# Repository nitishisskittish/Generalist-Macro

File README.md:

## **Astrapad**
---
A 7 key macropad with a rotary encoder, OLED screen, and 16 WS2812B LED’s. Currently runs on KMK firmware

### **Features**
---
- Two Piece 3D Printable Case
- 128x32 OLED Display
- EC11 Rotary encoder
- 16 WS2812B RGB LEDs, probably waaayyy too much, but the more the merrier I guess
- 7 Keys

### **CAD Model**
---
The case is held together by 4 M3 Bolts and heatset inserts, 1 in each corner. The bottom half of the case has a built in tilt. Originally I designed this with see-through plastic “windows” in mind, but as of now those windows have been replaced with direct holes looking into the PCB. Maybe I’ll add them later.

### **PCB**
---
I made my PCB in KiCad. I got the bangboo silkscreen arts from the [Zenless Zone Zero Fandom Sticker Page](https://zenless-zone-zero.fandom.com/wiki/Stickers), and the pikachu art from [pixlecheese](https://www.pixilart.com/art/pikachu-thunderbolt-1a236168d6612c3)

- Schematic:

- PCB:

- My favorite part of the whole project tbh, made me feel very smart. Also if you're interested the numbers at the very bottom are binary, although it doesn’t spell out anything that interesting

### **Firmware**
---
Currently Astrapad runs on KMK, but I plan on switching to QMK later because I want to add [VIA](https://caniusevia.com/) support
- The rotary encoder changes the volume, and you can tap it to toggle mute
- The top left and top right keys skips forward or backward respectively in the playback queue
- The top middle button and bottom 3 buttons act as WASD keys, with the top middle button being the W Key
- The bottom right button is currently mapped to a custom shortcut I have on my computer that opens Spotify
- The OLED Screen displays the current volume level of whatever device the macropad is currently connected to
- I have a list of features I want to add commented in the KMK main.py file if you're interested in that
### **BOM**
---
- 1x Seeed XIAO RP2040
- 1x 0.91 inch OLED displays 
- 1x EC11 rotary encoders
- 1x Case (2 3D printed parts)
- 1x 3D printed EC11 (Rotary Encoder) Knob
- 4x M3x5x4 Heatset inserts
- 4x M3x16mm screws
- 7x Cherry MX Switches
- 7x DSA keycaps
- 8x Through-hole 1N4148 Diodes
- 16x SK6812 MINI-E LEDs

### **Extra Stuff**
---
The example I’m basing this README off of had this section, so I’m adding it too. 
Thanks a lot to the Blueprint Hackclub slack, I probably wouldn’t have finished this project without their help.
Ummm yeah, that’s it I guess.

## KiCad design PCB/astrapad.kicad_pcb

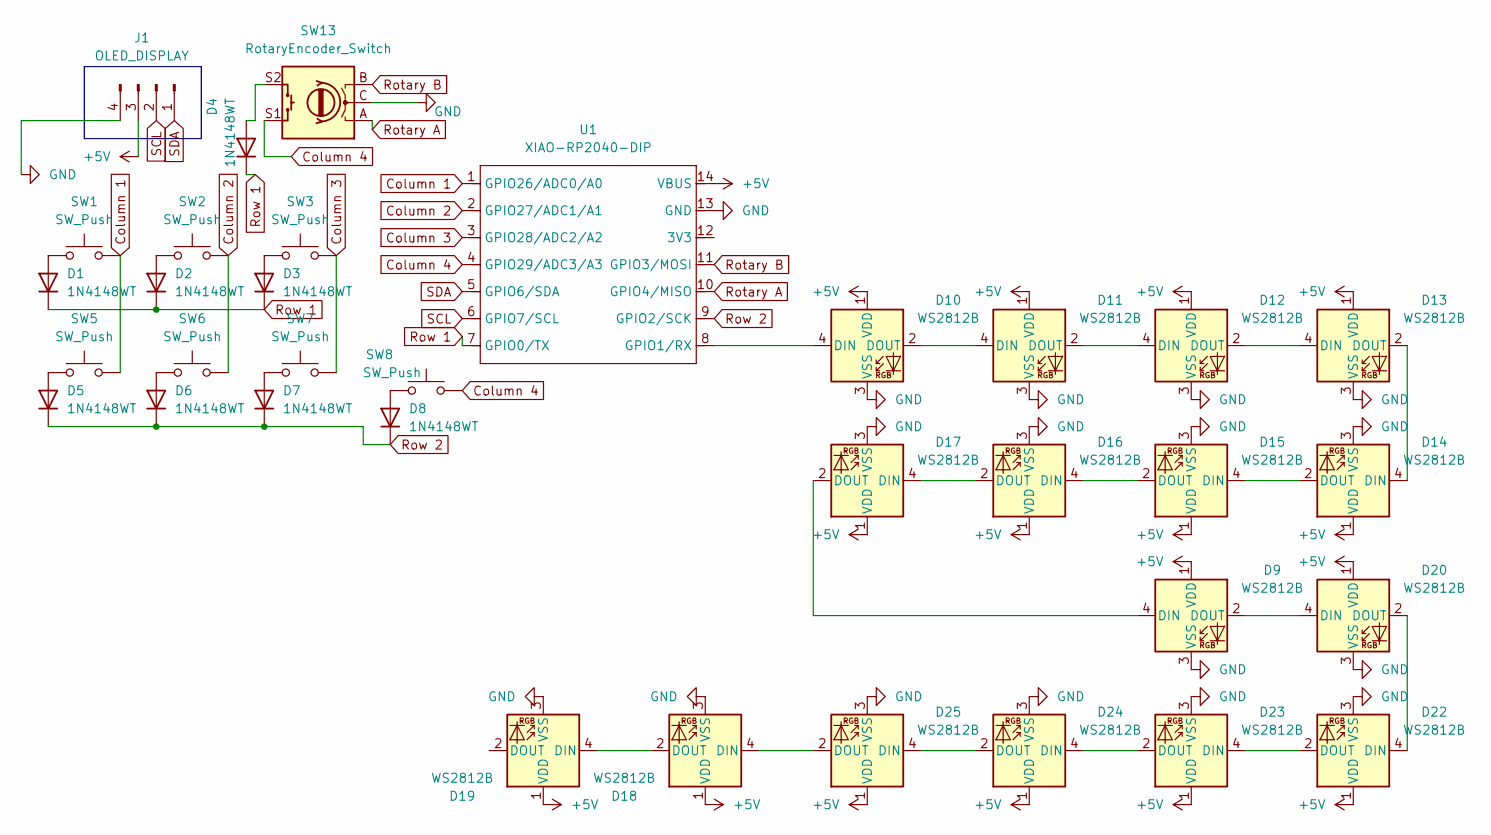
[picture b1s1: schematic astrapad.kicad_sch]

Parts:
D1, D2, D3, D4, D5, D6, D7, D8: 1N4148WT; D_SOD-523
D9, D17, D18, D19, D20, D22, D23, D24, D25: WS2812B; LED_SK6812MINI_PLCC4_3.5x3.5mm_P1.75mm
D10, D11, D12, D13, D14, D15, D16: WS2812B; MX_SK6812MINI-E_REV
J1: OLED_DISPLAY; PinHeader_1x04_P2.54mm_Vertical
SW1, SW2, SW3, SW5, SW6, SW7, SW8: SW_Push; SW_Cherry_MX_1.00u_PCB
SW13: RotaryEncoder_Switch; RotaryEncoder_Alps_EC11E-Switch_Vertical_H20mm
U1: XIAO-RP2040-DIP

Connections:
+5V: D9.1 (VDD), D10.1 (VDD), D11.1 (VDD), D12.1 (VDD), D13.1 (VDD), D14.1 (VDD), D15.1 (VDD), D16.1 (VDD), D17.1 (VDD), D18.1 (VDD), D19.1 (VDD), D20.1 (VDD), D22.1 (VDD), D23.1 (VDD), D24.1 (VDD), D25.1 (VDD), J1.3, U1.14 (VBUS)
Column 1: SW1.2, SW5.2, U1.1 (GPIO26/ADC0/A0)
Column 2: SW2.2, SW6.2, U1.2 (GPIO27/ADC1/A1)
Column 3: SW3.2, SW7.2, U1.3 (GPIO28/ADC2/A2)
Column 4: SW8.2, SW13.S1, U1.4 (GPIO29/ADC3/A3)
GND: D9.3 (VSS), D10.3 (VSS), D11.3 (VSS), D12.3 (VSS), D13.3 (VSS), D14.3 (VSS), D15.3 (VSS), D16.3 (VSS), D17.3 (VSS), D18.3 (VSS), D19.3 (VSS), D20.3 (VSS), D22.3 (VSS), D23.3 (VSS), D24.3 (VSS), D25.3 (VSS), J1.4, SW13.C, U1.13 (GND)
unnamed: D1.2 (A), SW1.1
unnamed: D2.2 (A), SW2.1
unnamed: D3.2 (A), SW3.1
unnamed: D4.2 (A), SW13.S2
unnamed: D5.2 (A), SW5.1
unnamed: D6.2 (A), SW6.1
unnamed: D7.2 (A), SW7.1
unnamed: D8.2 (A), SW8.1
unnamed: D10.4 (DIN), U1.8 (GPIO1/RX)
unnamed: D10.2 (DOUT), D11.4 (DIN)
unnamed: D11.2 (DOUT), D12.4 (DIN)
unnamed: D12.2 (DOUT), D13.4 (DIN)
unnamed: D13.2 (DOUT), D14.4 (DIN)
unnamed: D14.2 (DOUT), D15.4 (DIN)
unnamed: D15.2 (DOUT), D16.4 (DIN)
unnamed: D16.2 (DOUT), D17.4 (DIN)
unnamed: D9.4 (DIN), D17.2 (DOUT)
unnamed: D18.4 (DIN), D25.2 (DOUT)
unnamed: D18.2 (DOUT), D19.4 (DIN)
unnamed: D9.2 (DOUT), D20.4 (DIN)
unnamed: D20.2 (DOUT), D22.4 (DIN)
unnamed: D22.2 (DOUT), D23.4 (DIN)
unnamed: D23.2 (DOUT), D24.4 (DIN)
unnamed: D24.2 (DOUT), D25.4 (DIN)
Rotary A: SW13.A, U1.10 (GPIO4/MISO)
Rotary B: SW13.B, U1.11 (GPIO3/MOSI)
Row 1: D1.1 (K), D2.1 (K), D3.1 (K), D4.1 (K), U1.7 (GPIO0/TX)
Row 2: D5.1 (K), D6.1 (K), D7.1 (K), D8.1 (K), U1.9 (GPIO2/SCK)
SCL: J1.2, U1.6 (GPIO7/SCL)
SDA: J1.1, U1.5 (GPIO6/SDA)

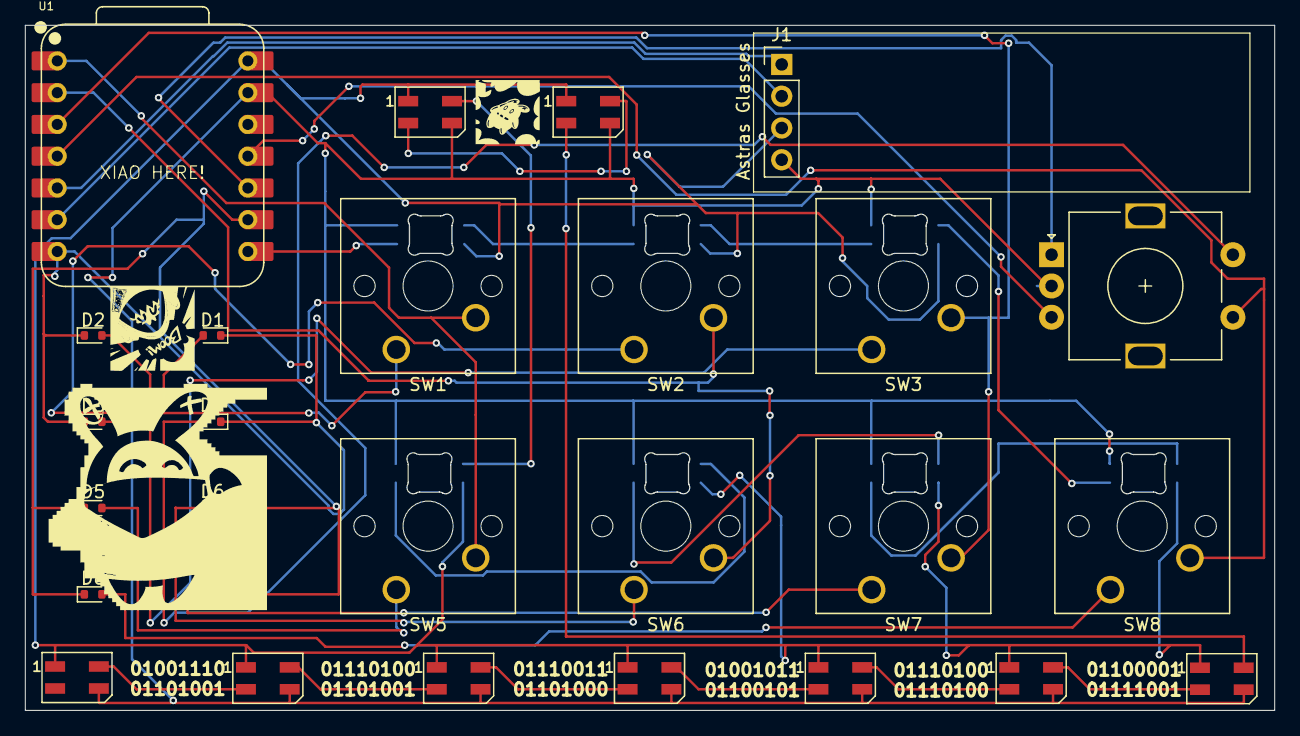
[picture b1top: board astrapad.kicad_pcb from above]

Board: 2 copper layers, 99.8 x 54.7 mm, 34 parts (0 on the bottom side), 36 nets.

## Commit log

2025-11-29 Finished Schematic, Started PCB
2025-11-30 PCB laid out and wired. I just have to add the **Aesthetic** silkscreens now
2025-12-06 Fixed 3D Model of PCB in FreeCAD Turns out the knob isn't centered properly, so I'll have to fix that later. In other news, I really shouldn't be awake this late...
2025-12-07 Switching from FreeCAD to Fusion360 Due to the several and constant issues I'm having with FreeCAD, I will be switching to Fusion360 If you wish to know why I was using FreeCAD in the first place, it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
2025-12-11 Repositioned Key Backlight LEDS
2025-12-12 Some PCB Rerouting And by "some", I mean all of it. I didn't account for the size of the actual OLED screen (just had the pins before), so I had to reroute basically everything once I did.
2025-12-20 Forgot to export with tracks
2025-12-22 Case finished, going to start working on readme, syncing to desktop
2025-12-22 A merge tragedy occurred...
2025-12-22 Yeah....I forgot to update the footprints after updating the paths. Also all these commits are happening because I'm syncing files between my laptop and desktop through git
2025-12-22 Ok, I fixed everything, now just need to finalize the README
2025-12-23 Every time I look at this README I find another mistake
